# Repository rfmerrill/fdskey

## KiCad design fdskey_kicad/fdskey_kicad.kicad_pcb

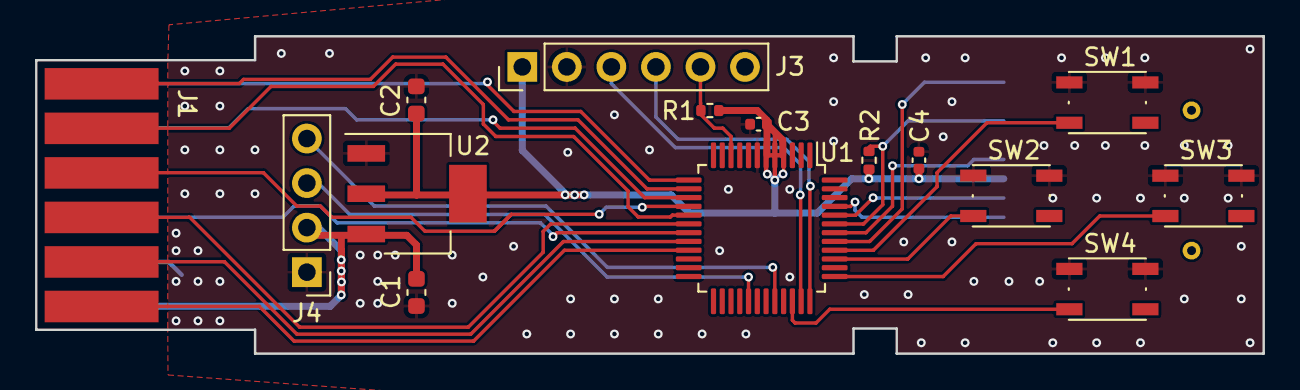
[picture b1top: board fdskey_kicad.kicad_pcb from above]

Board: 2 copper layers, 70.0 x 18.1 mm, 16 parts (1 on the bottom side), 26 nets.

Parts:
C1, C2: 4.7u; C_0603_1608Metric
C3, C4: 0.1u; C_0402_1005Metric
J1: FDS_RAM_ADAPTER; edgeconn_100mil_2x6
J2: Micro_SD_Card; 112J-TDAR-R01_ATT_fdskey
J3: ISP_HEADER; PinHeader_1x06_P2.54mm_Vertical
J4: DISPLAY; PinHeader_1x04_P2.54mm_Vertical
R1, R2: 2k5; R_0402_1005Metric
SW1, SW2, SW3, SW4: SW_Push; SW_Push_matching_fdskey
U1: STM32G0B0CETx; LQFP-48_7x7mm_P0.5mm
U2: LD1117S33TR_SOT223; SOT-223-3_TabPin2_fdskey

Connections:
+3V3: C2.1, C3.1, C4.1, J2.4, J3.1, R1.2, R2.2, U1.4 (VBAT), U1.5 (VREF+), U1.6 (VDD), U2.2 (VO)
+5V: C1.1, J1.2, J4.2, U2.3 (VI)
/MOTOR_ON: J1.6, U1.19 (PB0)
/READ_DATA: J1.9, U1.17 (PA6)
/WRITE_DATA: J1.5, U1.18 (PA7)
/~MEDIA_SET: J1.10, U1.15 (PA4)
/~READY: J1.11, U1.14 (PA3)
/~SCAN_MEDIA: J1.3, U1.20 (PB1)
/~STOP_MOTOR: J1.12, U1.13 (PA2)
/~WRITABLE_MEDIA: J1.7, U1.16 (PA5)
/~WRITE: J1.1, U1.21 (PB2)
BUTTON_1: SW1.2, U1.40 (PD2)
BUTTON_2: SW2.2, U1.39 (PD1)
BUTTON_3: SW3.2, U1.37 (PA15)
BUTTON_4: SW4.2, U1.34 (PA12/PA10)
GND: C1.2, C2.2, C3.2, C4.2, J1.4, J2.6, J3.2, J4.1, SW1.1, SW2.1, SW3.1, SW4.1, U1.7 (VSS), U2.1 (GND)
I2C_SCL: J4.3, U1.29 (PA9/NC)
I2C_SDA: J4.4, U1.32 (PA10/NC)
NRST: J3.5, R1.1, U1.10 (NRST)
SD_CLK: J2.5, U1.42 (PB3)
SD_CS: J2.2, U1.45 (PB6)
SD_DTCT: J2.9, U1.41 (PD3)
SD_MISO: J2.7, R2.1, U1.43 (PB4)
SD_MOSI: J2.3, U1.44 (PB5)
SWCLK: J3.4, U1.36 (PA14)
SWDIO: J3.3, U1.35 (PA13)

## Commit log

2023-09-17 Start conversion to kicad.
2023-09-17 (mostly) passes DRC!
